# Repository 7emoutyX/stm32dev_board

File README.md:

STM32L432KBU_NRF24L01P_Development_Board

## Overview
This repository contains the KiCad project files and firmware source code for the STM32L432KBU development board integrated with the NRF24L01P module. 

## Schematic 

[Download Schematic.pdf](https://github.com/7emoutyX/stm32dev_board/files/14748390/Final.Schematic.pdf)

## Layaout :  

## Features
- Development board based on STM32L432KBU microcontroller
- Integrated NRF24L01P wireless communication module
- Antenna socket
- JTAG debug pins
- Schematics and PCB layout designed with KiCad

## Getting Started
To get started with this development board, follow these steps:

1. Clone this repository to your local machine.
2. Open the KiCad project files located in the `Documentation/Schematics` and `Documentation/PCB Layout` directories.
3. Review the schematics and PCB layout to understand the hardware design.

## Documentation
- **Schematics:** KiCad schematic files (.sch)
- **PCB Layout:** KiCad PCB layout files (.kicad_pcb)
- **Datasheets:**:
- Datasheets for STM32L432KBU : (https://www.mouser.fr/datasheet/2/389/stm32l432kb-1851151.pdf)
- Datasheets NRF24L01P  : (https://www.mouser.fr/datasheet/2/297/nRF24L01P-1187709.pdf)

## Issues
Found a bug or have a feature request? Please open an issue [here](../../issues)!

## Final results :

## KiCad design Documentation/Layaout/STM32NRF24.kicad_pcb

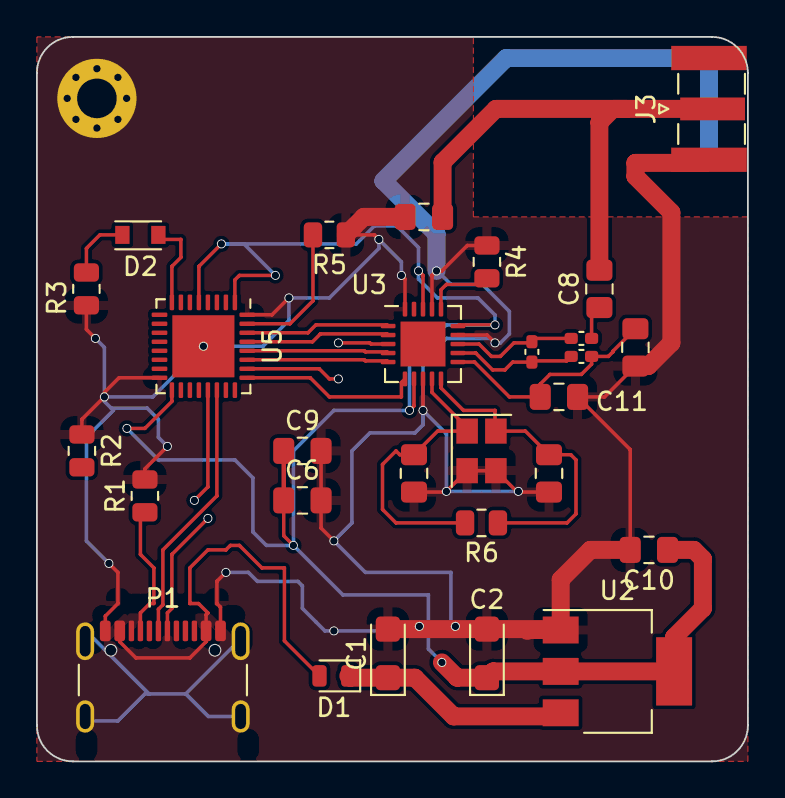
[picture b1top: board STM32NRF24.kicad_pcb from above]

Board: 4 copper layers, 39.5 x 40.2 mm, 28 parts (0 on the bottom side), 24 nets.

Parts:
C1, C2: 47uF; CP_EIA-3216-18_Kemet-A
C3, C5, C6, C7, C8, C9, C10, C11, C12: C; C_0805_2012Metric_Pad1.18x1.45mm_HandSolder
D1: BAV300; D_MicroMELF
D2: LED; LED_miniPLCC_2315
J3: Conn_Coaxial; SMA_Samtec_SMA-J-P-X-ST-EM1_EdgeMount
L1, L2, L3: L; C_0402_1005Metric_Pad0.74x0.62mm_HandSolder
P1: USB_C_Plug_USB2.0; USB_C_Receptacle_GCT_USB4105-xx-A_16P_TopMnt_Horizontal
R1, R2, R3, R4, R5, R6: 100; R_0805_2012Metric
U2: LD1117S12TR_SOT223; SOT-223-3_TabPin2
U3: nRF24L01P; QFN-20-1EP_4x4mm_P0.5mm_EP2.5x2.5mm
U5: STM32L432KBUx; QFN-32-1EP_5x5mm_P0.5mm_EP3.45x3.45mm
Y2: Crystal_GND23_Small; Crystal_SMD_Abracon_ABM8AIG-4Pin_3.2x2.5mm

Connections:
3.3v: C2.1, C6.1, C9.1, C10.1, U2.2 (VO), U3.7 (VDD), U3.15 (VDD), U3.18 (VDD), U5.1 (VDD), U5.5 (VDDA), U5.17 (VDD)
D+: P1.A6 (D+), U5.22 (PA12)
D-: P1.A7 (D-), U5.21 (PA11)
GND: C1.2, C2.2, C3.2, C5.2, C6.2, C7.2, C9.2, C10.2, C11.2, C12.2, J3.2 (Ext), P1.A1 (GND), P1.A12 (GND), P1.B1 (GND), P1.B12 (GND), R1.2, R2.1, R3.1, R4.1, R5.1, U2.1 (GND), U3.8 (VSS), U3.14 (VSS), U3.17 (VSS), U3.20 (VSS), U5.16 (VSS), U5.32 (VSS), U5.33 (VSS), Y2.2, Y2.3
NRF_CE: U3.1 (CE), U5.30 (PB7)
NRF_IRQ: U3.6 (IRQ), U5.25 (PA15)
unnamed: C8.1, L3.2
unnamed: D1.2 (A), P1.A4 (VBUS), P1.A9 (VBUS), P1.B4 (VBUS), P1.B9 (VBUS)
unnamed: C1.1, D1.1 (K), U2.3 (VI)
unnamed: D2.2 (A), U5.8 (PA2)
unnamed: D2.1 (K), R3.2
unnamed: C7.1, C8.2, J3.1 (In)
unnamed: P1.A5 (CC), R1.1
unnamed: L1.1, L2.1, U3.12 (ANT1)
unnamed: L1.2, L3.1, U3.13 (ANT2)
unnamed: R4.2, U3.16 (IREF)
unnamed: C11.1, C12.1, L2.2, U3.11 (VDD_PA)
unnamed: C5.1, R6.1, U3.10 (XC1), Y2.4
unnamed: C3.1, R6.2, U3.9 (XC2), Y2.1
unnamed: R5.2, U5.31 (PH3)
SPI_CSK: U3.3 (SCK), U5.26 (PB3)
SPI_CSn: U3.2 (CSN), U5.29 (PB6)
SPI_MISO: U3.5 (MISO), U5.27 (PB4)
SPI_MOSI: U3.4 (MOSI), U5.28 (PB5)

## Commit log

2024-03-25 README.md
